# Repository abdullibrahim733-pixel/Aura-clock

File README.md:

# Aura Clock
### *The desk that fight back*

> "Five more minutes"
> i said that at 9:05
> it was 11:47 pm before i looked up

---

## The problem that built This

i was a 18 years old building hardware in Arusha 

i have a robot to build, a simulator to build, a hackerthon to qualify for 

and yet i know what youtube autoplay algorithm looks like in 2AM i know the exact moment a quick break becomes a 2hr detour i know that interanl voice say i will work on this after this one video and just five more minutes and i will work better late at night

That voice is a liar.

Software timers dont fix this. i dismissed paradogm apps with in a week grayscale modes lasted several days website bloockers tool 30 secondsevery solution i have made has the same flaw it could be ignored,**

A notification can be swiped, A popup can be closed, An allert can be muted.

**A physical shutter can not.**

AuraClock is an opensource mechatronics IOT hub that enforces deep work by creating an **undeniable physical-digital feedback loop.**

it watches your active window, it watches your active window title silently in the background. If your working - coding, writting, Designing the device displays a calm OLED face and everything is quite.

The momment you navigate to a blacklisted website or window the machine responds physicaly and also software where it closses mandatory the blacklisted sites and window

1. **The shutter closses.** A micro-servo drives a rack and pinion transmition rotating an opaque mask across the oled display behind a smoked screen the screen physically disaprears

2. **The heptic fires** An LRA vibration mottor pulls 3 Agresive pulses not a gentle buzz, a strucuted allert your hand feels through the desk 

3. **The Aura ledger** records the breach and drops your points in the dashboard

Return your Work. The shutter opens the calm face returns. the session resumes 

there is no dissmiss buttons and no snooze there is no "Remind me later"

there is only: **get back to work**

---

# System Architecture

---

┌─────────────────────────────────────────────────────────┐
│                     HOST MACHINE                        │
│                                                         │
│   ┌──────────────────────────────────────────────┐      │
│   │          auraclock-daemon.py                 │      │
│   │                                              │      │
│   │  Active window title polling (500ms)         │      │
│   │  Allowlist / blocklist evaluation            │      │
│   │  Session timer + Aura ledger                 │      │
│   │  WebSocket client (ws://auraclock.local)     │      │
│   └──────────────────────┬───────────────────────┘      │
│                           │ Local WiFi                  │
└───────────────────────────┼─────────────────────────────┘
                            │ WebSocket (async JSON)
                            ▼
┌─────────────────────────────────────────────────────────┐
│                  ESP32-WROOM-32E                        │
│               (Custom PCB, local fab)                   │
│                                                         │
│   WebSocket Server ──► State Machine                    │
│                              │                          │
│              ┌───────────────┼───────────────┐          │
│              ▼               ▼               ▼          │
│         SSD1306 OLED   SG90 Servo       ERM Motor       │
│         (OLED face)  (Shutter drive)  (Haptic pulse)    │
│                            │                            │
│                    Rack-and-Pinion                      │
│                    Transmission                         │
│                            │                            │
│                    Opaque Shutter Mask                  │
└─────────────────────────────────────────────────────────┘
```
## hardware

### Custom PCB

Designed in kicad fabricated localy in Arusha, Tanzania.
single sided, 0.5mm minimum trace width, hand etched and assembled

**Core components**

 Component | Part | Purpose |
|-----------|------|---------|
| MCU | ESP32-WROOM-32E | Main brain, WiFi, WebSocket server |
| USB Bridge | CH340C (SOIC-16) | Programming interface |
| Regulator | AMS1117-3.3 (SOT-223) | 3.3V power rail |
| Display | SSD1306 OLED 0.96" (I2C) | OLED face + Aura score |
| Actuator | SG90 Micro Servo | Drives rack-and-pinion shutter |
| Haptic | ERM Coin Vibration Motor | Tactile feedback |
| Driver | S8050 NPN + 1N4148 | Motor switching circuit |
| Power | USB-C connector | 5V input |

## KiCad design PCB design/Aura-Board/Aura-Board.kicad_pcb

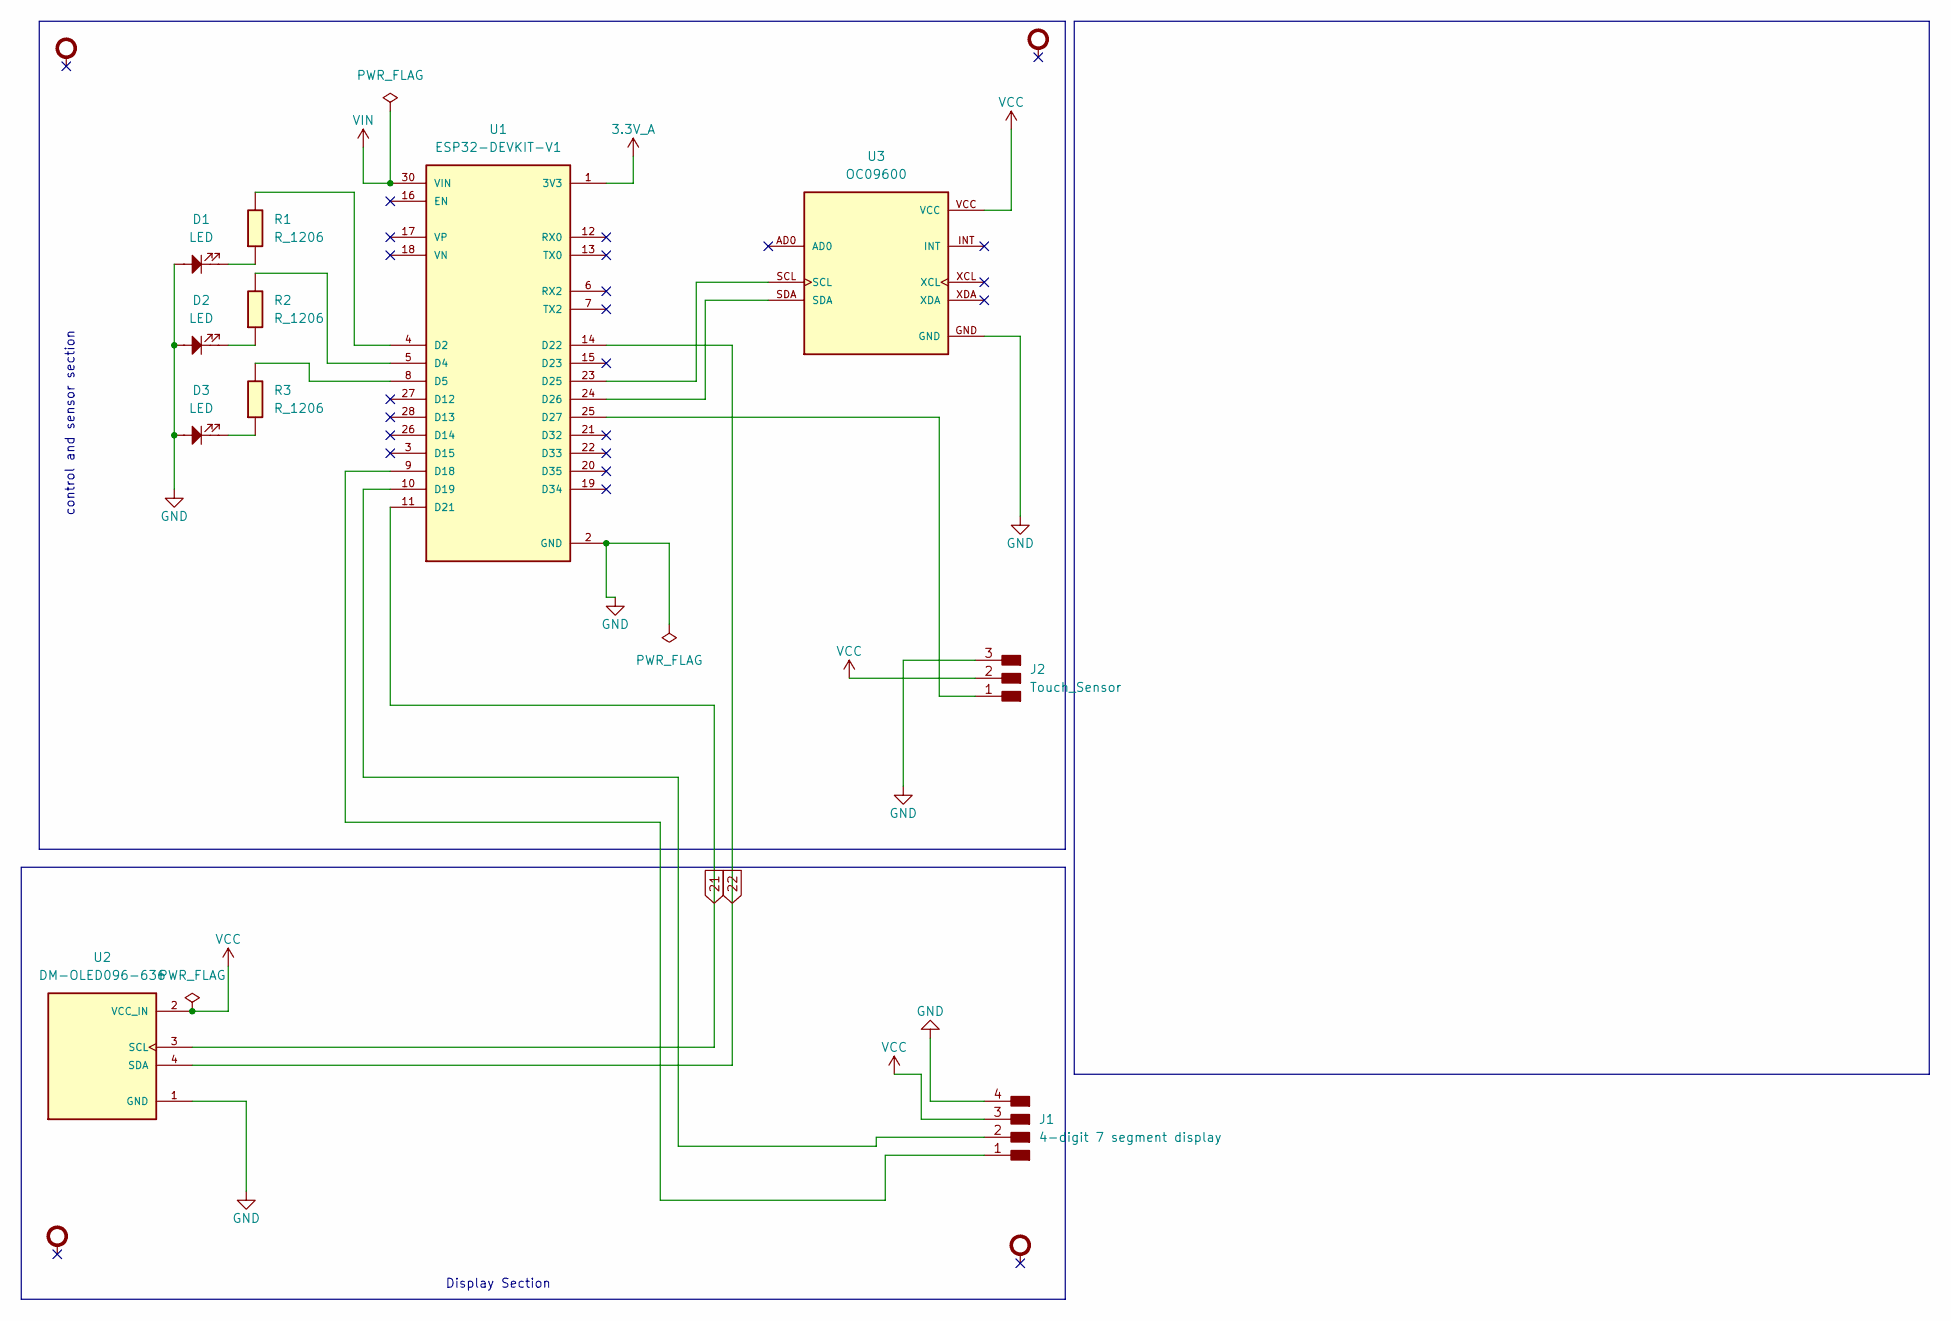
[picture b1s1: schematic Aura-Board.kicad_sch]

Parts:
D1, D2, D3: LED; LED_5mm_RightAngle
J1: 4-digit 7 segment display; PinHeader_01x04_P2.54mm_Vertical_THT_D1.4mm
J2: Touch_Sensor; PinHeader_01x03_P2.54mm_Vertical_THT_D1mm
R1, R2, R3: R_1206
ST1, ST2, ST3, ST4: Standoff; Standoff_Connected
U1: ESP32-DEVKIT-V1; MODULE_ESP32_DEVKIT_V1; PARTREV N/A
U2: DM-OLED096-636; MODULE_DM-OLED096-636; PARTREV 2018-09-10
U3: OC09600; MODULE_OC09600; PARTREV NA

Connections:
3.3V_A: U1.1 (3V3)
21: U1.11 (D21), U2.3 (SCL)
22: U1.14 (D22), U2.4 (SDA)
GND: D1.2, D2.2, D3.2, J1.4, J2.3, U1.2 (GND), U1.29 (GND), U2.1 (GND), U3.GND
unnamed: D1.1, R1.2
unnamed: D2.1, R2.2
unnamed: D3.1, R3.2
unnamed: J1.1, U1.9 (D18)
unnamed: J1.2, U1.10 (D19)
unnamed: J2.1, U1.25 (D27)
unnamed: R1.1, U1.4 (D2)
unnamed: R2.1, U1.5 (D4)
unnamed: R3.1, U1.8 (D5)
unnamed: U1.23 (D25), U3.SCL
unnamed: U1.24 (D26), U3.SDA
VCC: J1.3, J2.2, U2.2 (VCC_IN), U3.VCC
VIN: U1.30 (VIN)

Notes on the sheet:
Display Section
control and sensor section

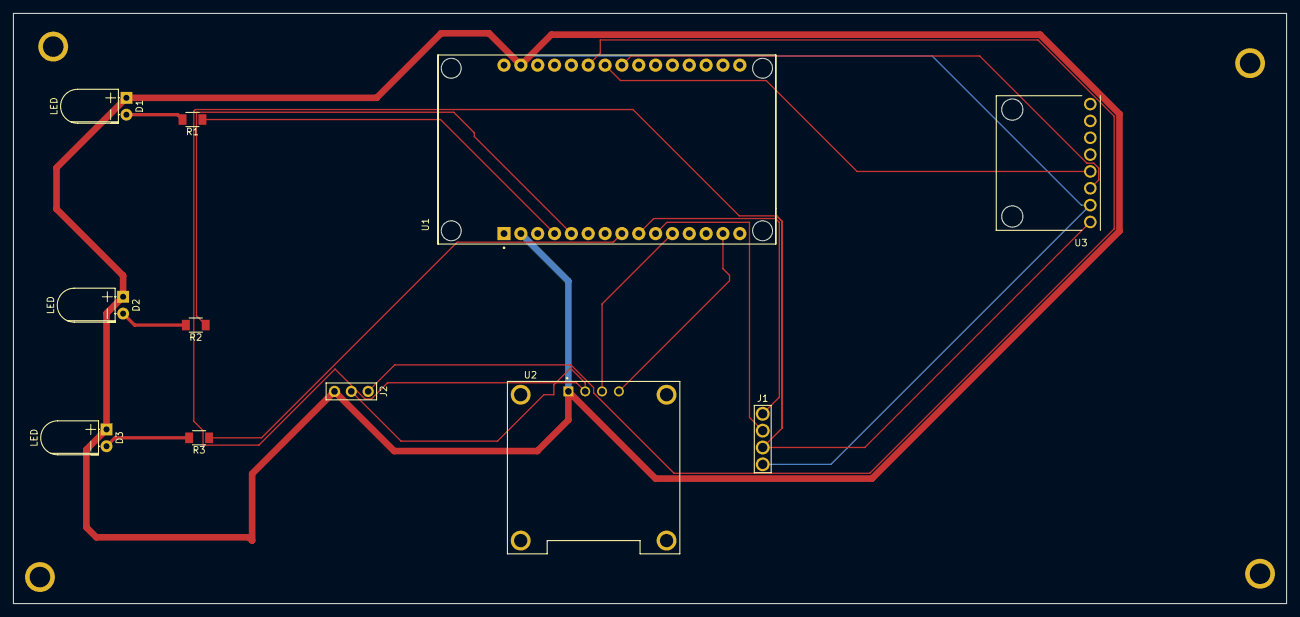
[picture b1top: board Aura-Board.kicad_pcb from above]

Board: 2 copper layers, 192.0 x 89.0 mm, 15 parts (0 on the bottom side), 15 nets.

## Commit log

2026-05-18 wrote the dameon for Aura clock
2026-05-23 removed aura dimmension
2026-05-25 production
2026-05-26 update PCB design files
